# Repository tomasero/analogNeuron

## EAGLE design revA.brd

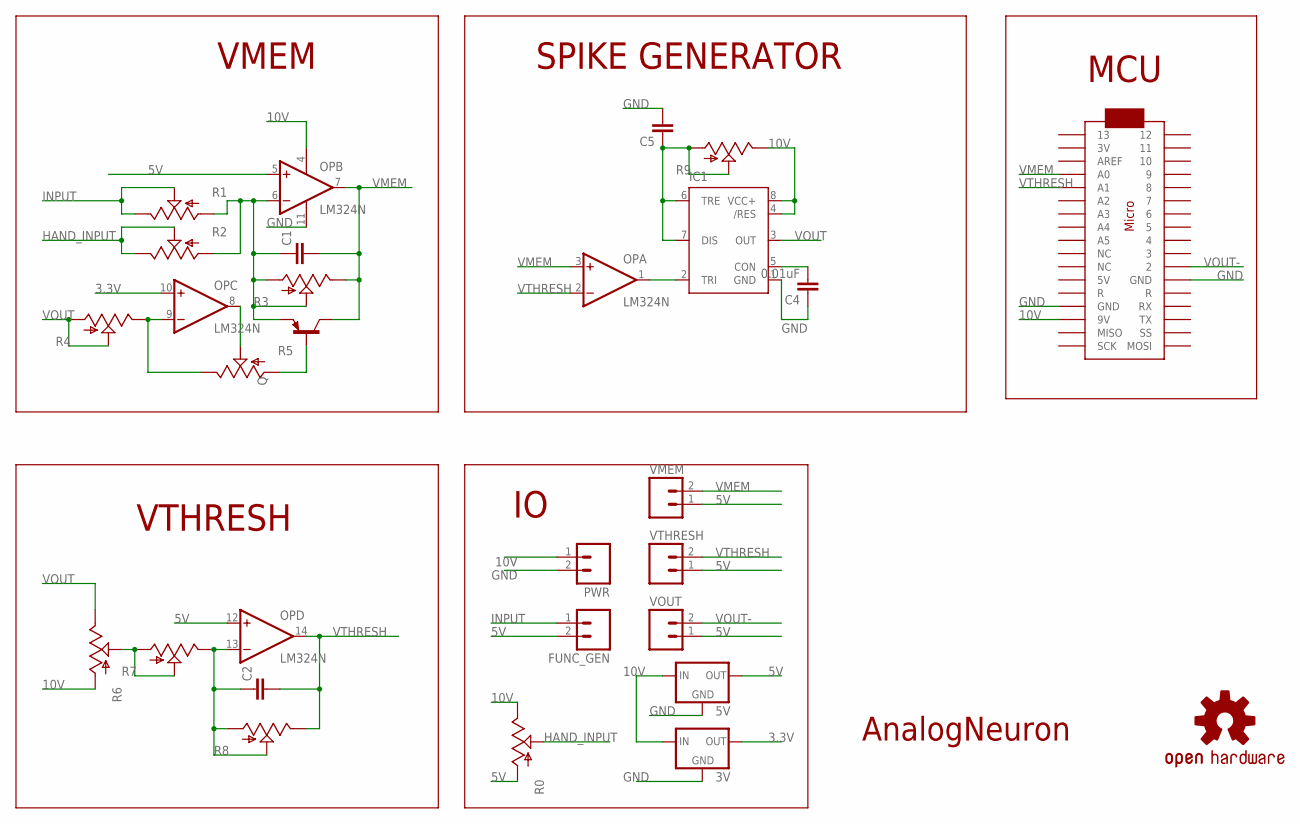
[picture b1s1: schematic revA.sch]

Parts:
3V, 5V: 78LXX
C1, C2, C5: CAPPTH1; CAP-PTH-5MM
C4: 0.01uF; CAP-PTH-5MM
FUNC_GEN: M023.5MM; SCREWTERMINAL-3.5MM-2
IC1: NE555KIT; DIP08-KIT
LOGO1: OSHW-LOGOL-TOP; OSHW_LOGO_L_TOP
OP: LM324N; DIL14
PWR: M023.5MM; SCREWTERMINAL-3.5MM-2
Q: 2N3906-PNP-TO92-EBC; TO92-EBC
R0, R1, R2, R3, R4, R5, R6, R7, R8, R9: POT; ALPS_POT
U$1: ARDUINOMICRO
VMEM: M023.5MM; SCREWTERMINAL-3.5MM-2
VOUT: M023.5MM; SCREWTERMINAL-3.5MM-2
VTHRESH: M023.5MM; SCREWTERMINAL-3.5MM-2

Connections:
2: C1.1, OP.6 (-IN), Q.E, R1.P$3 (A), R2.P$3 (A), R3.P$2 (S), R3.P$3 (A)
3.3V: 3V.OUT, OP.10 (+IN)
5V: 5V.OUT, FUNC_GEN.2, OP.5 (+IN), OP.12 (+IN), R0.P$3 (A), VMEM.1, VOUT.1, VTHRESH.1
10V: 3V.IN, 5V.IN, IC1.4 (/RES), IC1.8 (VCC+), OP.4 (V+), PWR.1, R0.P$1 (E), R6.P$3 (A), R9.P$1 (E), U$1.P$20 (9V)
CON: C4.2, IC1.5 (CON)
GND: 3V.GND, 5V.GND, C4.1, C5.2, IC1.1 (GND), OP.11 (V-), PWR.2, U$1.P$12 (GND), U$1.P$21 (GND)
HAND_INPUT: R0.P$2 (S), R2.P$1 (E), R2.P$2 (S)
INPUT: FUNC_GEN.1, R1.P$1 (E), R1.P$2 (S)
unnamed: C5.1, IC1.6 (TRE), IC1.7 (DIS), R9.P$2 (S), R9.P$3 (A)
unnamed: Q.B, R5.P$3 (A)
unnamed: OP.9 (-IN), R4.P$1 (E), R5.P$1 (E)
unnamed: C2.1, OP.13 (-IN), R7.P$1 (E), R8.P$2 (S), R8.P$3 (A)
R7: R6.P$2 (S), R7.P$2 (S), R7.P$3 (A)
TRI: IC1.2 (TRI), OP.1 (OUT)
VMEM: C1.2, OP.3 (+IN), OP.7 (OUT), Q.C, R3.P$1 (E), U$1.P$31 (A0), VMEM.2
VOUT: IC1.3 (OUT), R4.P$2 (S), R4.P$3 (A), R6.P$1 (E)
VOUT-: OP.8 (OUT), R5.P$2 (S), U$1.P$11 (2), VOUT.2
VTHRESH: C2.2, OP.2 (-IN), OP.14 (OUT), R8.P$1 (E), U$1.P$30 (A1), VTHRESH.2

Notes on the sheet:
MCU
VTHRESH
VMEM
AnalogNeuron
SPIKE GENERATOR

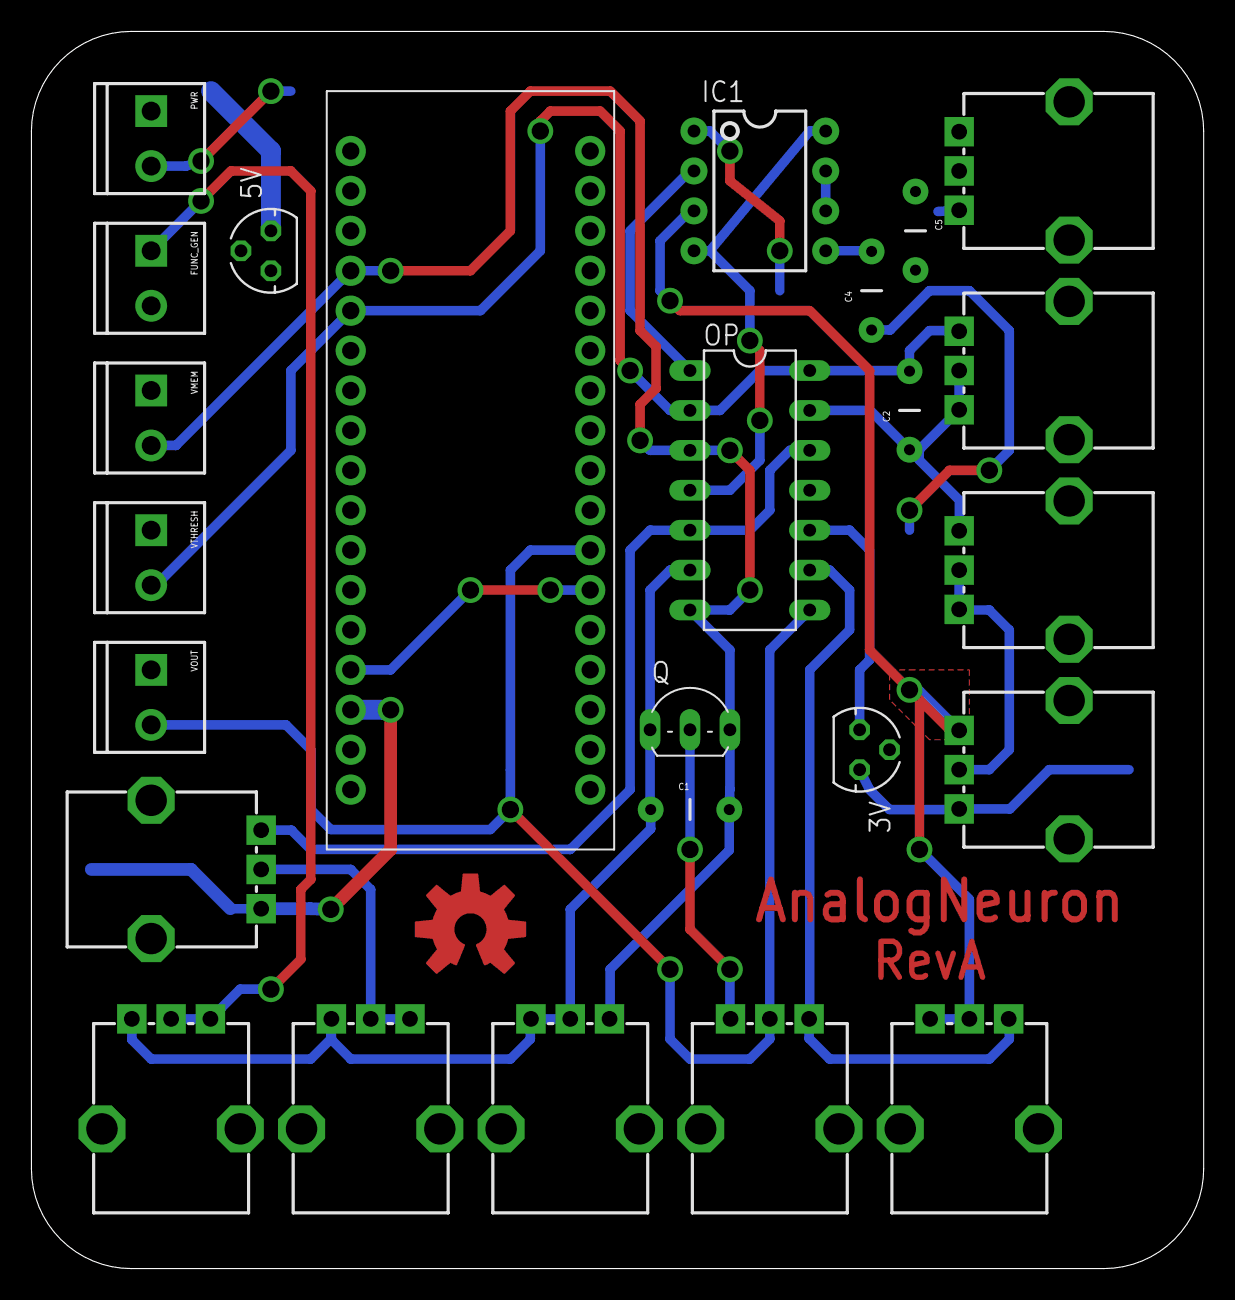
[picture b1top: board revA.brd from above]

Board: 2 copper layers, 74.6 x 78.7 mm, 26 parts (0 on the bottom side), 18 nets.

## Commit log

2016-12-06 revA
2016-12-07 revA done
2016-12-07 fixed drc

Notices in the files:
parts and their libraries:
SparkFun-AnalogIC: Licensing:Creative Commons ShareAlike 4.0 International - https://creativecommons.org/licenses/by-sa/4.0
microbuilder: This work is placed in the public domain, and may be freely used for commercial and non-commercial work with the following conditions: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
